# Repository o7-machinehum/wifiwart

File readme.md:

# Wifiwart
## Custom Non Form Factor Board

## Final boards

The WiFiWart is an open source WiFi penetration device masquerading as a 
wall charger. It features a 1.2Ghz Cortex A7 MPU with two WiFi
chips. The electrical, mechanical and software elemenet are all completely
open source. Check out the blog series!

- [Final Blog Post](https://interruptlabs.ca/2021/10/25/I-put-a-WiFi-router-into-a-phone-charger-Final-Post/)
- [Blog Post #3](https://interruptlabs.ca/2021/09/22/I'm-not-putting-a-WiFi-router-into-a-phone-charger-Part-3/)
- [Blog Post #2](https://interruptlabs.ca/2021/07/19/I'm-putting-a-WiFi-router-into-a-wall-charger-Part-2/)
- [Blog Post #1](https://interruptlabs.ca/2021/06/15/I'm-putting-a-WiFi-router-into-a-wall-charger-Part-1/)
- [Blog Post #0](https://interruptlabs.ca/2021/04/28/I'm-putting-a-WiFi-router-into-a-wall-charger-Part-0/)
- [Join us on Discord!](https://discord.gg/EtZT7mjNuM)

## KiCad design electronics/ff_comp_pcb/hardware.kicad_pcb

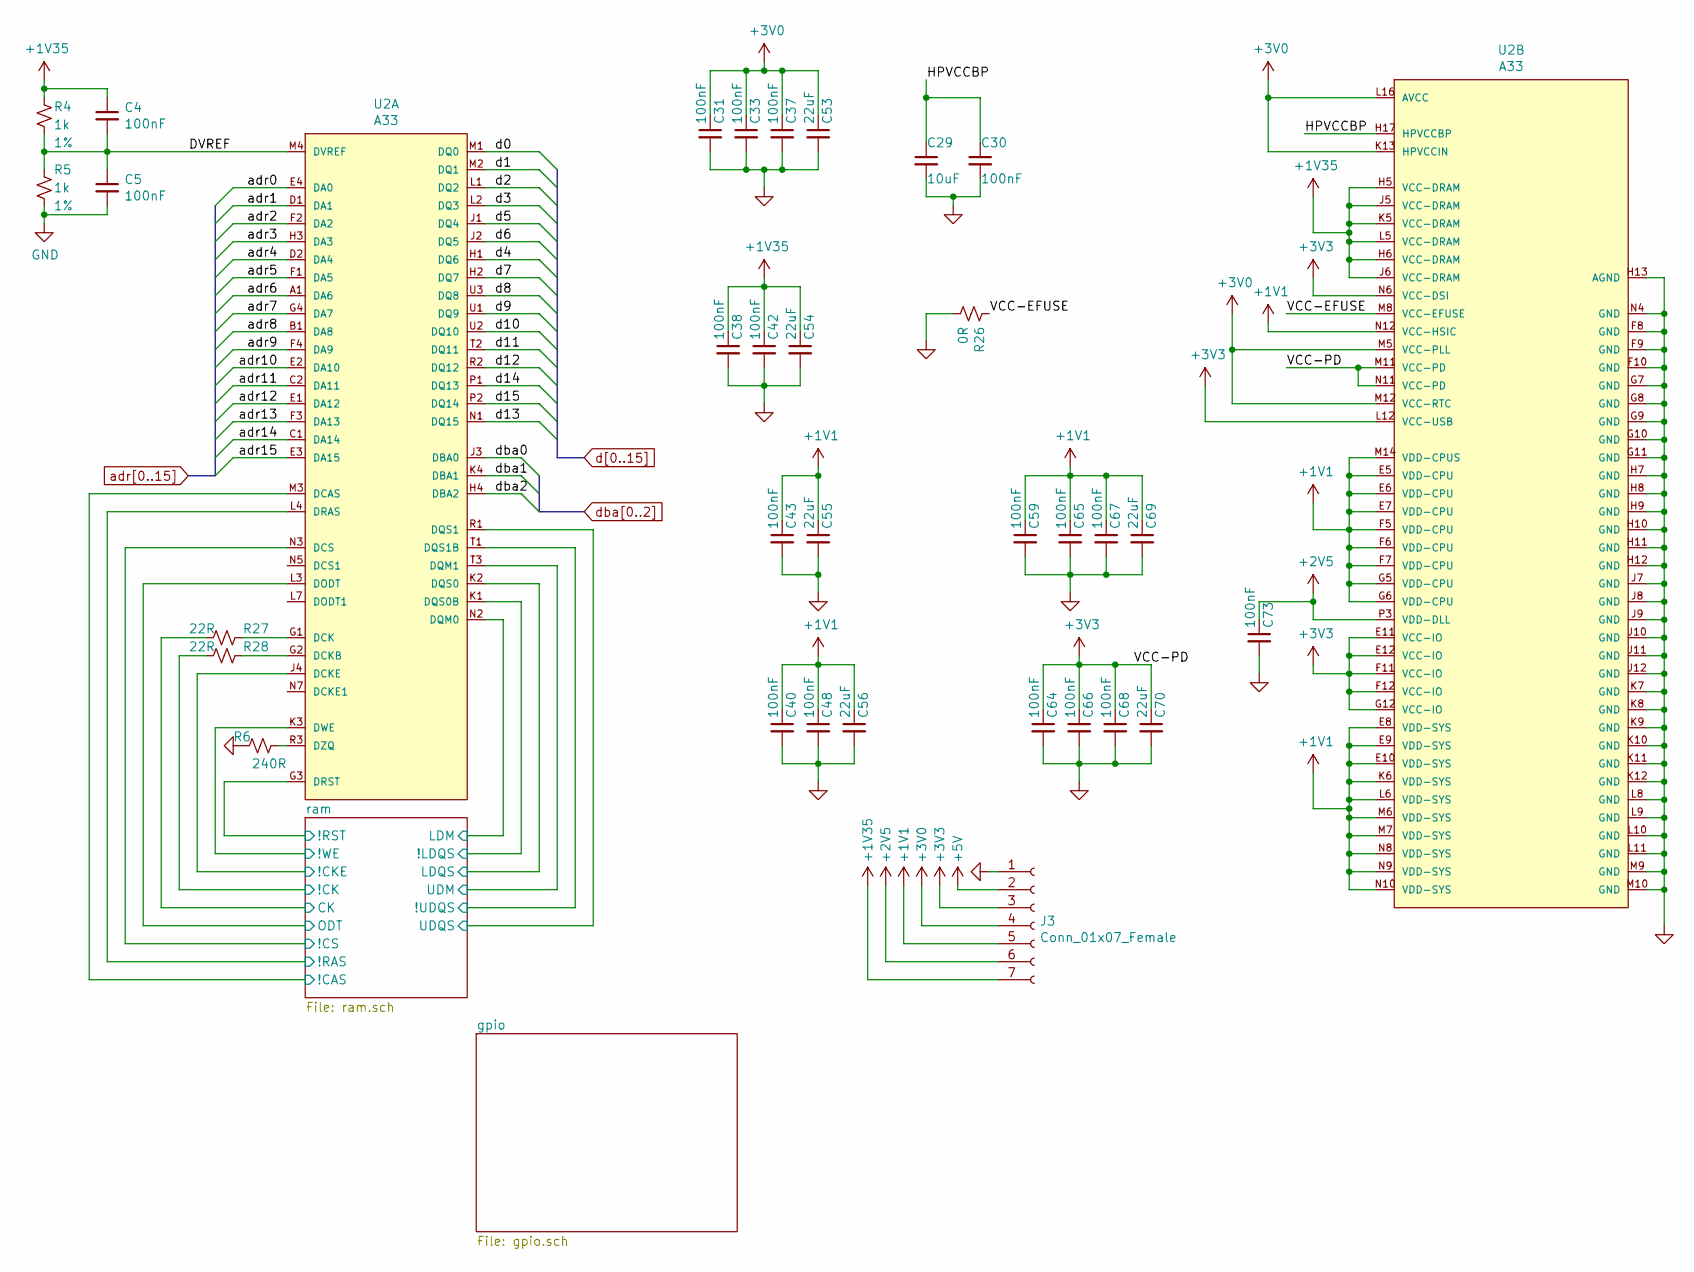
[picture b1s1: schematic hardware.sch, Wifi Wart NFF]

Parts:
C4, C5, C30, C31, C33, C37, C38, C40, C42, C43, C48, C59, C64, C65, C66, C67, C68, C73: 100nF; C_0402_1005Metric; MPN CC0402KRX7R7BB104
C29: 10uF; C_0402_1005Metric; MPN CL05A106MQ5NUNC
C53, C54, C55, C56, C69, C70: 22uF; C_0402_1005Metric; MPN GRM155R60J226ME11D
J3: Conn_01x07_Female; PinHeader_1x07_P2.54mm_Vertical
R4, R5: 1k; R_0402_1005Metric; Tolerance 1%; MPN 4-1879208-9
R6: 240R; R_0402_1005Metric; MPN 0402WGF2400TCE
R26: 0R; R_0402_1005Metric; MPN RC0402JR-070RL
R27, R28: 22R; R_0402_1005Metric; MPN RC0402JR-0722RL
U2: A33; Allwinner_Technology_Co.,_Ltd.-A33-0; MPN A33

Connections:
+1V1: C40.1, C43.1, C48.1, C55.1, C56.1, C59.1, C65.1, C67.1, C69.1, J3.5, U2.E5 (VDD-CPU), U2.E6 (VDD-CPU), U2.E7 (VDD-CPU), U2.E8 (VDD-SYS), U2.E9 (VDD-SYS), U2.E10 (VDD-SYS), U2.F5 (VDD-CPU), U2.F6 (VDD-CPU), U2.F7 (VDD-CPU), U2.G5 (VDD-CPU), U2.G6 (VDD-CPU), U2.K6 (VDD-SYS), U2.L6 (VDD-SYS), U2.M6 (VDD-SYS), U2.M7 (VDD-SYS), U2.M14 (VDD-CPUS), U2.N8 (VDD-SYS), U2.N9 (VDD-SYS), U2.N10 (VDD-SYS), U2.N12 (VCC-HSIC)
+1V35: C4.1, C38.1, C42.1, C54.1, J3.7, R4.1, U2.H5 (VCC-DRAM), U2.H6 (VCC-DRAM), U2.J5 (VCC-DRAM), U2.J6 (VCC-DRAM), U2.K5 (VCC-DRAM), U2.L5 (VCC-DRAM); also elsewhere on the board
+2V5: C73.1, J3.6, U2.P3 (VDD-DLL)
+3V0: C31.1, C33.1, C37.1, C53.1, J3.4, U2.K13 (HPVCCIN), U2.L16 (AVCC), U2.M5 (VCC-PLL), U2.M12 (VCC-RTC)
+3V3: C64.1, C66.1, C68.1, C70.1, J3.3, U2.E11 (VCC-IO), U2.E12 (VCC-IO), U2.F11 (VCC-IO), U2.F12 (VCC-IO), U2.G12 (VCC-IO), U2.L12 (VCC-USB), U2.M11 (VCC-PD), U2.N6 (VCC-DSI), U2.N11 (VCC-PD); also elsewhere on the board
+5V: J3.2; also elsewhere on the board
/DVREF: C4.2, C5.1, R4.2, R5.1, U2.M4 (DVREF)
/HPVCCBP: C29.1, C30.1, U2.H17 (HPVCCBP)
/VCC-EFUSE: R26.1, U2.M8 (VCC-EFUSE)
/ram/!CAS: U2.M3 (DCAS); also elsewhere on the board
/ram/!CK: R28.2; also elsewhere on the board
/ram/!CKE: U2.J4 (DCKE); also elsewhere on the board
/ram/!CS: U2.N3 (DCS); also elsewhere on the board
/ram/!LDQS: U2.K1 (DQS0B); also elsewhere on the board
/ram/!RAS: U2.L4 (DRAS); also elsewhere on the board
/ram/!RST: U2.G3 (DRST); also elsewhere on the board
/ram/!UDQS: U2.T1 (DQS1B); also elsewhere on the board
/ram/!WE: U2.K3 (DWE); also elsewhere on the board
/ram/CK: R27.2; also elsewhere on the board
/ram/LDM: U2.N2 (DQM0); also elsewhere on the board
/ram/LDQS: U2.K2 (DQS0); also elsewhere on the board
/ram/ODT: U2.L3 (DODT); also elsewhere on the board
/ram/UDM: U2.T3 (DQM1); also elsewhere on the board
/ram/UDQS: U2.R1 (DQS1); also elsewhere on the board
GND: C5.2, C29.2, C30.2, C31.2, C33.2, C37.2, C38.2, C40.2, C42.2, C43.2, C48.2, C53.2, C54.2, C55.2, C56.2, C59.2, C64.2, C65.2, C66.2, C67.2, C68.2, C69.2, C70.2, C73.2, J3.1, R5.2, R6.2, R26.2, U2.F8 (GND), U2.F9 (GND), U2.F10 (GND), U2.G7 (GND), U2.G8 (GND), U2.G9 (GND), U2.G10 (GND), U2.G11 (GND), U2.H7 (GND), U2.H8 (GND), U2.H9 (GND), U2.H10 (GND), U2.H11 (GND), U2.H12 (GND), U2.H13 (AGND), U2.J7 (GND), U2.J8 (GND), U2.J9 (GND), U2.J10 (GND), U2.J11 (GND), U2.J12 (GND), U2.K7 (GND), U2.K8 (GND), U2.K9 (GND), U2.K10 (GND), U2.K11 (GND), U2.K12 (GND), U2.L8 (GND), U2.L9 (GND), U2.L10 (GND), U2.L11 (GND), U2.M9 (GND), U2.M10 (GND), U2.N4 (GND); also elsewhere on the board
unnamed: R6.1, U2.R3 (DZQ)
unnamed: R27.1, U2.G1 (DCK)
unnamed: R28.1, U2.G2 (DCKB)
adr0: U2.E4 (DA0); also elsewhere on the board
adr1: U2.D1 (DA1); also elsewhere on the board
adr2: U2.F2 (DA2); also elsewhere on the board
adr3: U2.H3 (DA3); also elsewhere on the board
adr4: U2.D2 (DA4); also elsewhere on the board
adr5: U2.F1 (DA5); also elsewhere on the board
adr6: U2.A1 (DA6); also elsewhere on the board
adr7: U2.G4 (DA7); also elsewhere on the board
adr8: U2.B1 (DA8); also elsewhere on the board
adr9: U2.F4 (DA9); also elsewhere on the board
adr10: U2.E2 (DA10); also elsewhere on the board
adr11: U2.C2 (DA11); also elsewhere on the board
adr12: U2.E1 (DA12); also elsewhere on the board
adr13: U2.F3 (DA13); also elsewhere on the board
adr14: U2.C1 (DA14); also elsewhere on the board
adr15: U2.E3 (DA15); also elsewhere on the board
d0: U2.M1 (DQ0); also elsewhere on the board
d1: U2.M2 (DQ1); also elsewhere on the board
d2: U2.L1 (DQ2); also elsewhere on the board
d3: U2.L2 (DQ3); also elsewhere on the board
d4: U2.H1 (DQ6); also elsewhere on the board
d5: U2.J1 (DQ4); also elsewhere on the board
d6: U2.J2 (DQ5); also elsewhere on the board
d7: U2.H2 (DQ7); also elsewhere on the board
d8: U2.U3 (DQ8); also elsewhere on the board
d9: U2.U1 (DQ9); also elsewhere on the board
d10: U2.U2 (DQ10); also elsewhere on the board
d11: U2.T2 (DQ11); also elsewhere on the board
d12: U2.R2 (DQ12); also elsewhere on the board
d13: U2.N1 (DQ15); also elsewhere on the board
d14: U2.P1 (DQ13); also elsewhere on the board
d15: U2.P2 (DQ14); also elsewhere on the board
dba0: U2.J3 (DBA0); also elsewhere on the board
dba1: U2.K4 (DBA1); also elsewhere on the board
dba2: U2.H4 (DBA2); also elsewhere on the board

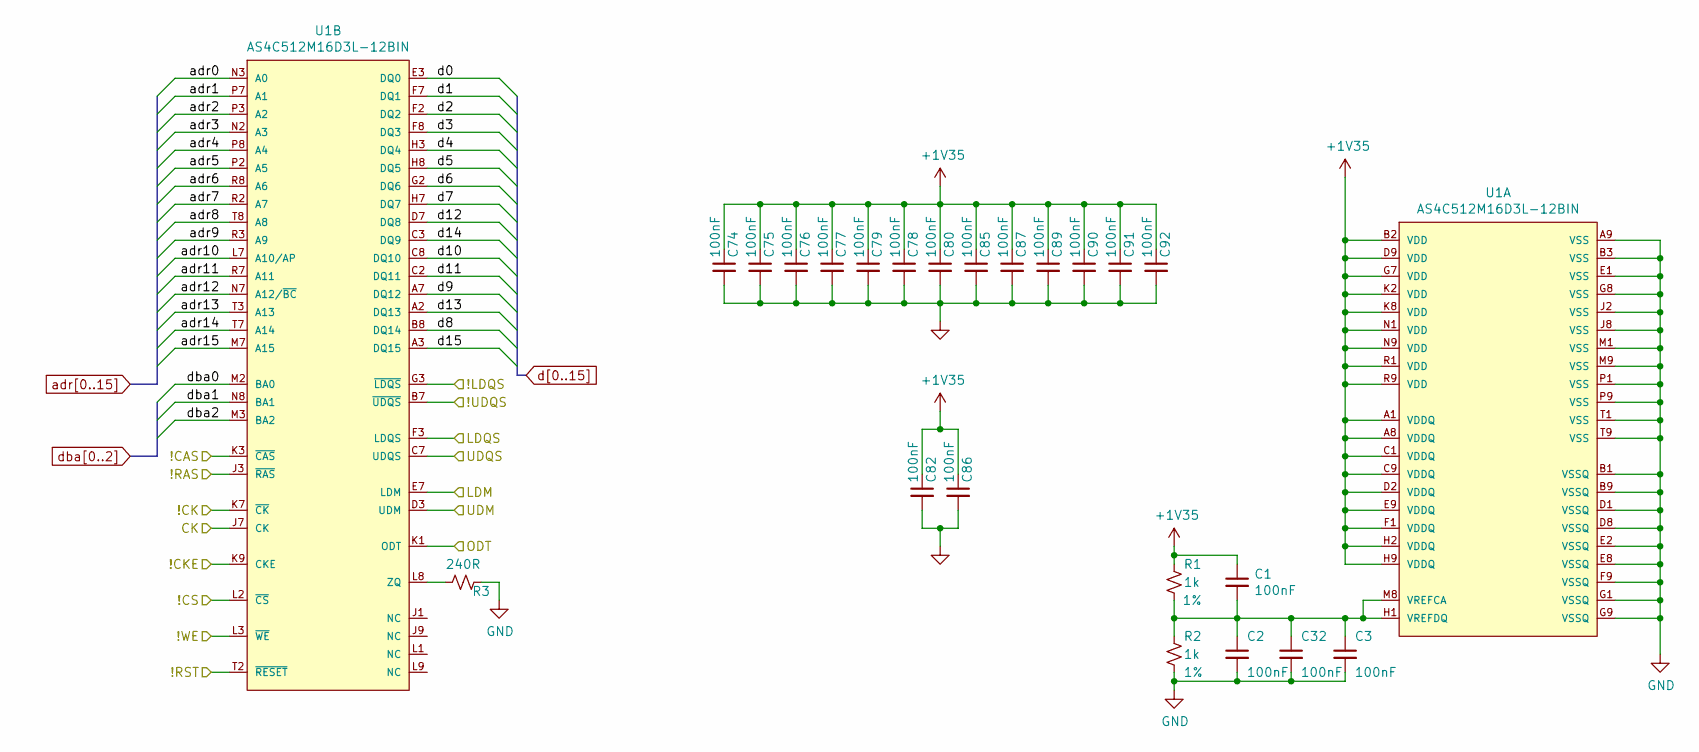
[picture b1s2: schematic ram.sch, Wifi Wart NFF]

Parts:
C1, C2, C3, C32, C74, C75, C76, C77, C78, C79, C80, C82, C85, C86, C87, C89, C90, C91, C92: 100nF; C_0402_1005Metric; MPN CC0402KRX7R7BB104
R1, R2: 1k; R_0402_1005Metric; Tolerance 1%; MPN 4-1879208-9
R3: 240R; R_0402_1005Metric; MPN 0402WGF2400TCE
U1: AS4C512M16D3L-12BIN; Alliance_Memory-AS4C512M16D3L-12BIN-0-0-IPC_A; MPN AS4C512M16D3L-12BIN

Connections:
+1V35: C1.1, C74.1, C75.1, C76.1, C77.1, C78.1, C79.1, C80.1, C82.1, C85.1, C86.1, C87.1, C89.1, C90.1, C91.1, C92.1, R1.1, U1.A1 (VDDQ), U1.A8 (VDDQ), U1.B2 (VDD), U1.C1 (VDDQ), U1.C9 (VDDQ), U1.D2 (VDDQ), U1.D9 (VDD), U1.E9 (VDDQ), U1.F1 (VDDQ), U1.G7 (VDD), U1.H2 (VDDQ), U1.H9 (VDDQ), U1.K2 (VDD), U1.K8 (VDD), U1.N1 (VDD), U1.N9 (VDD), U1.R1 (VDD), U1.R9 (VDD); also elsewhere on the board
/ram/!CAS: U1.K3 (~CAS~); also elsewhere on the board
/ram/!CK: U1.K7 (~CK~); also elsewhere on the board
/ram/!CKE: U1.K9 (CKE); also elsewhere on the board
/ram/!CS: U1.L2 (~CS~); also elsewhere on the board
/ram/!LDQS: U1.G3 (~LDQS~); also elsewhere on the board
/ram/!RAS: U1.J3 (~RAS~); also elsewhere on the board
/ram/!RST: U1.T2 (~RESET~); also elsewhere on the board
/ram/!UDQS: U1.B7 (~UDQS~); also elsewhere on the board
/ram/!WE: U1.L3 (~WE~); also elsewhere on the board
/ram/CK: U1.J7 (CK); also elsewhere on the board
/ram/LDM: U1.E7 (LDM); also elsewhere on the board
/ram/LDQS: U1.F3 (LDQS); also elsewhere on the board
/ram/ODT: U1.K1 (ODT); also elsewhere on the board
/ram/UDM: U1.D3 (UDM); also elsewhere on the board
/ram/UDQS: U1.C7 (UDQS); also elsewhere on the board
GND: C2.2, C3.2, C32.2, C74.2, C75.2, C76.2, C77.2, C78.2, C79.2, C80.2, C82.2, C85.2, C86.2, C87.2, C89.2, C90.2, C91.2, C92.2, R2.2, R3.1, U1.A9 (VSS), U1.B1 (VSSQ), U1.B3 (VSS), U1.B9 (VSSQ), U1.D1 (VSSQ), U1.D8 (VSSQ), U1.E1 (VSS), U1.E2 (VSSQ), U1.E8 (VSSQ), U1.F9 (VSSQ), U1.G1 (VSSQ), U1.G8 (VSS), U1.G9 (VSSQ), U1.J2 (VSS), U1.J8 (VSS), U1.M1 (VSS), U1.M9 (VSS), U1.P1 (VSS), U1.P9 (VSS), U1.T1 (VSS), U1.T9 (VSS); also elsewhere on the board
unnamed: C1.2, C2.1, C3.1, C32.1, R1.2, R2.1, U1.H1 (VREFDQ), U1.M8 (VREFCA)
unnamed: R3.2, U1.L8 (ZQ)
adr0: U1.N3 (A0); also elsewhere on the board
adr1: U1.P7 (A1); also elsewhere on the board
adr2: U1.P3 (A2); also elsewhere on the board
adr3: U1.N2 (A3); also elsewhere on the board
adr4: U1.P8 (A4); also elsewhere on the board
adr5: U1.P2 (A5); also elsewhere on the board
adr6: U1.R8 (A6); also elsewhere on the board
adr7: U1.R2 (A7); also elsewhere on the board
adr8: U1.T8 (A8); also elsewhere on the board
adr9: U1.R3 (A9); also elsewhere on the board
adr10: U1.L7 (A10/AP); also elsewhere on the board
adr11: U1.R7 (A11); also elsewhere on the board
adr12: U1.N7 (A12/~BC~); also elsewhere on the board
adr13: U1.T3 (A13); also elsewhere on the board
adr14: U1.T7 (A14); also elsewhere on the board
adr15: U1.M7 (A15); also elsewhere on the board
d0: U1.E3 (DQ0); also elsewhere on the board
d1: U1.F7 (DQ1); also elsewhere on the board
d2: U1.F2 (DQ2); also elsewhere on the board
d3: U1.F8 (DQ3); also elsewhere on the board
d4: U1.H3 (DQ4); also elsewhere on the board
d5: U1.H8 (DQ5); also elsewhere on the board
d6: U1.G2 (DQ6); also elsewhere on the board
d7: U1.H7 (DQ7); also elsewhere on the board
d8: U1.B8 (DQ14); also elsewhere on the board
d9: U1.A7 (DQ12); also elsewhere on the board
d10: U1.C8 (DQ10); also elsewhere on the board
d11: U1.C2 (DQ11); also elsewhere on the board
d12: U1.D7 (DQ8); also elsewhere on the board
d13: U1.A2 (DQ13); also elsewhere on the board
d14: U1.C3 (DQ9); also elsewhere on the board
d15: U1.A3 (DQ15); also elsewhere on the board
dba0: U1.M2 (BA0); also elsewhere on the board
dba1: U1.N8 (BA1); also elsewhere on the board
dba2: U1.M3 (BA2); also elsewhere on the board

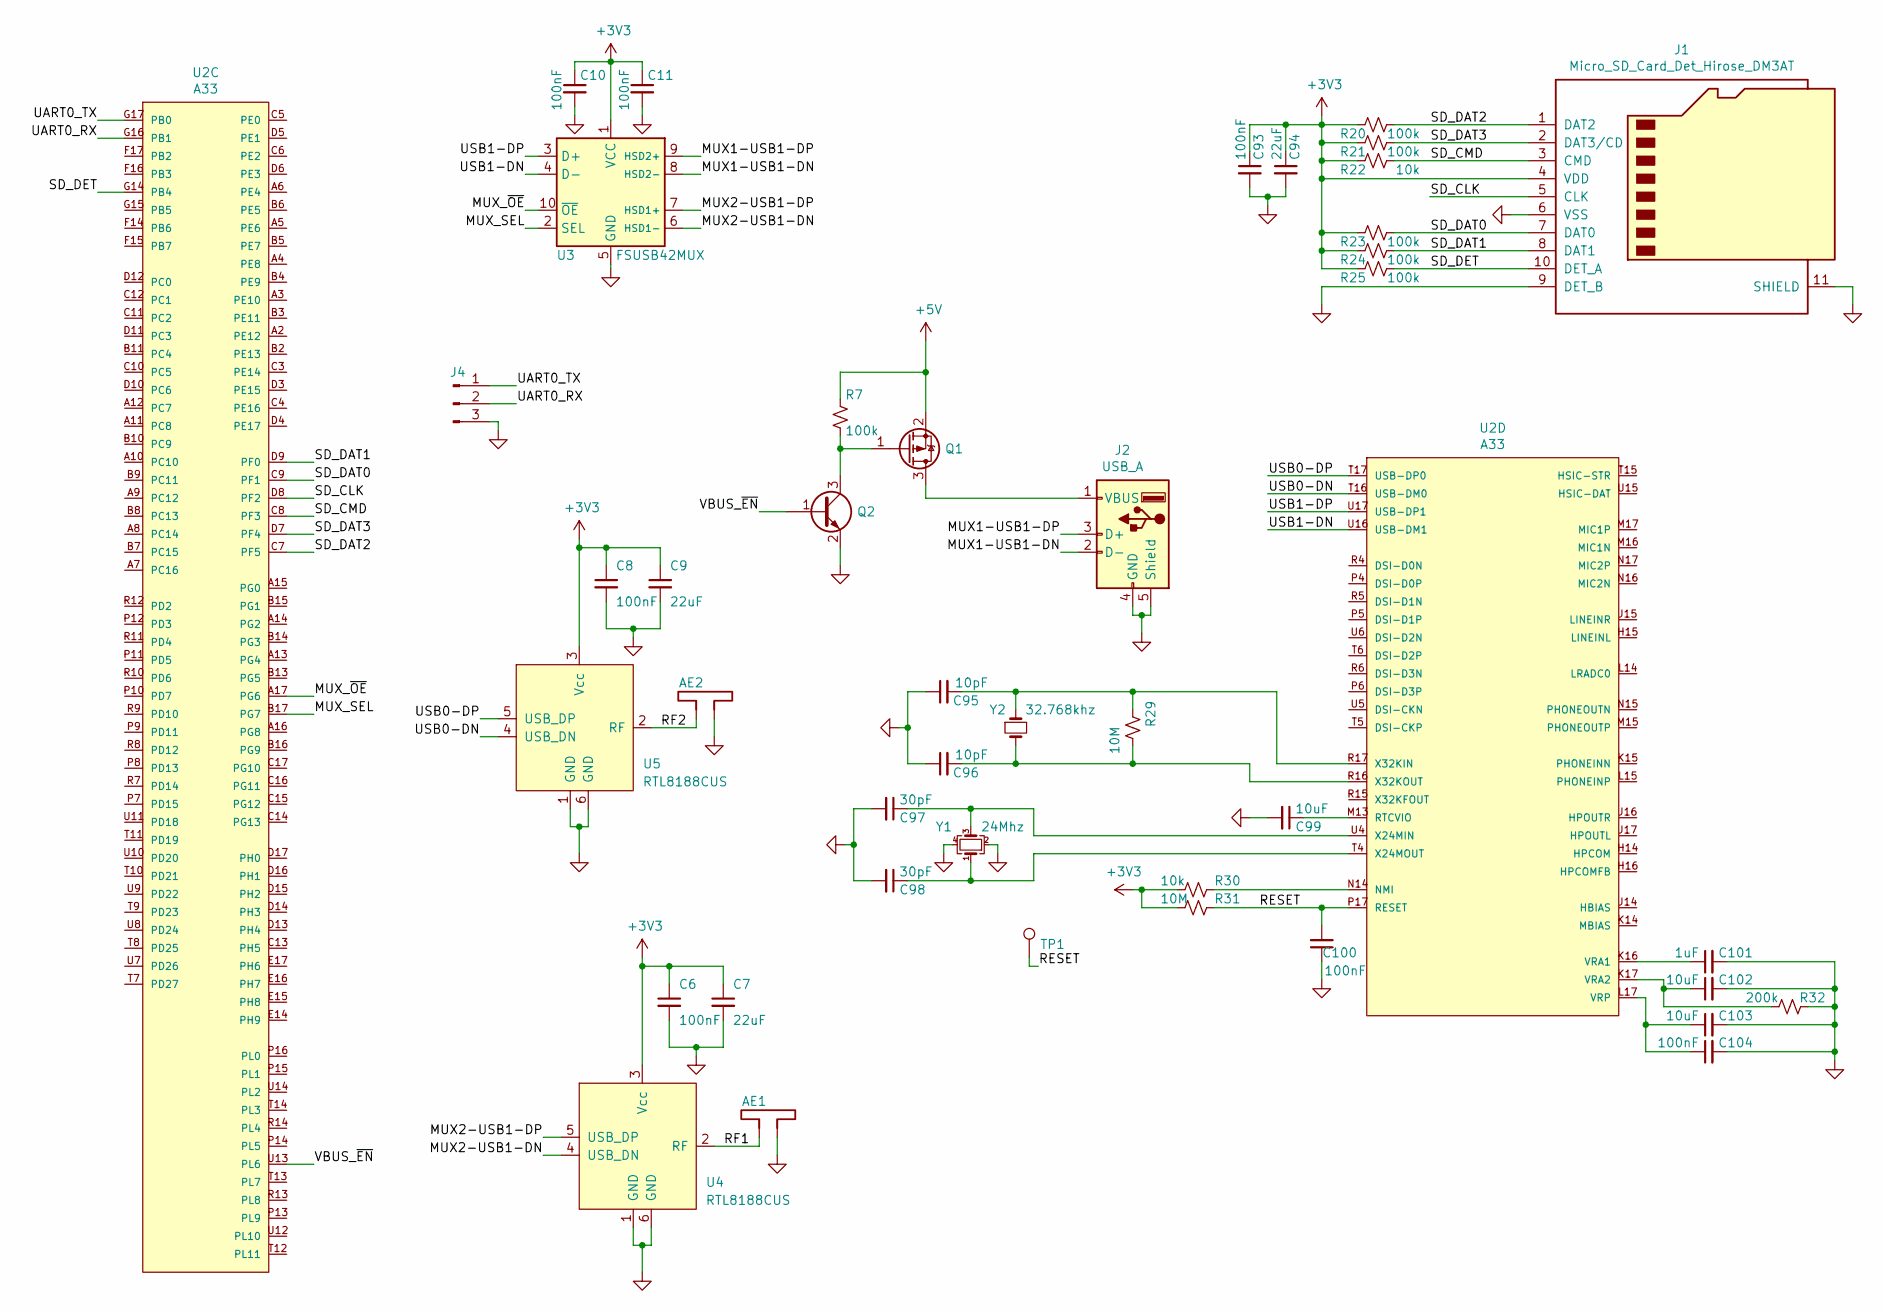
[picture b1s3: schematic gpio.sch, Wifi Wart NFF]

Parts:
AE1, AE2: Antenna_Dipole; U.FL_Hirose_U.FL-R-SMT-1_Vertical; MPN U.FL-R-SMT-1(10)
C6, C8, C10, C11, C93, C100, C104: 100nF; C_0402_1005Metric; MPN CC0402KRX7R7BB104
C7, C9, C94: 22uF; C_0402_1005Metric; MPN GRM155R60J226ME11D
C95, C96: 10pF; C_0402_1005Metric; MPN CC0402JRNPO9BN100
C97, C98: 30pF; C_0402_1005Metric; MPN CC0402JRNPO9BN300
C99, C102, C103: 10uF; C_0402_1005Metric; MPN CL05A106MQ5NUNC
C101: 1uF; C_0402_1005Metric; MPN CL05A105KO5NNNC
J1: Micro_SD_Card_Det_Hirose_DM3AT; microSD_HC_Hirose_DM3AT-SF-PEJM5; MPN DM3AT-SF-PEJM5
J2: USB_A; USB_A_Molex_67643_Horizontal; MPN 676430910
J4: Conn_01x03_Male; PinHeader_1x03_P2.54mm_Vertical
Q1: Q_PMOS_GSD; SOT-23; MPN SSM3J328R,LF
Q2: Q_NPN_BEC; SOT-23; MPN MMBT2369ALT1G
R7, R20, R21, R23, R24, R25: 100k; R_0402_1005Metric; MPN CR0402-JW-104GLF
R22, R30: 10k; R_0402_1005Metric; MPN RC0402JR-0710KL
R29, R31: 10M; R_0402_1005Metric; MPN 0402WGJ0106TCE
R32: 200k; R_0402_1005Metric; MPN RC0402FR-07200KL
TP1: TestPoint; TestPoint_Pad_2.0x2.0mm
U2: A33; Allwinner_Technology_Co.,_Ltd.-A33-0; MPN A33
U3: FSUSB42MUX; MSOP-10_3x3mm_P0.5mm; MPN FSUSB42MUX
U4, U5: RTL8188CUS; MPN RTL8188CUS
Y1: 24Mhz; Crystal_SMD_Abracon_ABM8G-4Pin_3.2x2.5mm; MPN ABM8G-24.000MHZ-18-D2Y-T
Y2: 32.768khz; Abracon-ABS05-0-0-MFG; MPN ABS05-32.768KHZ-9-T

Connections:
+3V3: C6.1, C7.1, C8.1, C9.1, C10.1, C11.1, C93.1, C94.1, J1.4 (VDD), R20.1, R21.1, R22.1, R23.1, R24.1, R25.1, R30.2, R31.2, U3.1 (VCC), U4.3 (Vcc), U5.3 (Vcc); also elsewhere on the board
+5V: Q1.2 (S), R7.1; also elsewhere on the board
/gpio/MUX1-USB1-DN: J2.2 (D-), U3.8 (HSD2-)
/gpio/MUX1-USB1-DP: J2.3 (D+), U3.9 (HSD2+)
/gpio/MUX2-USB1-DN: U3.6 (HSD1-), U4.4 (USB_DN)
/gpio/MUX2-USB1-DP: U3.7 (HSD1+), U4.5 (USB_DP)
/gpio/MUX_SEL: U2.B17 (PG7), U3.2 (SEL)
/gpio/MUX_~OE: U2.A17 (PG6), U3.10 (~OE)
/gpio/RESET: C100.2, R31.1, TP1.1, U2.P17 (RESET)
/gpio/RF1: AE1.1, U4.2 (RF)
/gpio/RF2: AE2.1, U5.2 (RF)
/gpio/SD_CLK: J1.5 (CLK), U2.D8 (PF2)
/gpio/SD_CMD: J1.3 (CMD), R22.2, U2.C8 (PF3)
/gpio/SD_DAT0: J1.7 (DAT0), R23.2, U2.C9 (PF1)
/gpio/SD_DAT1: J1.8 (DAT1), R24.2, U2.D9 (PF0)
/gpio/SD_DAT2: J1.1 (DAT2), R20.2, U2.C7 (PF5)
/gpio/SD_DAT3: J1.2 (DAT3/CD), R21.2, U2.D7 (PF4)
/gpio/SD_DET: J1.10 (DET_A), R25.2, U2.G14 (PB4)
/gpio/UART0_RX: J4.2, U2.G16 (PB1)
/gpio/UART0_TX: J4.1, U2.G17 (PB0)
/gpio/USB0-DN: U2.T16 (USB-DM0), U5.4 (USB_DN)
/gpio/USB0-DP: U2.T17 (USB-DP0), U5.5 (USB_DP)
/gpio/USB1-DN: U2.U16 (USB-DM1), U3.4 (D-)
/gpio/USB1-DP: U2.U17 (USB-DP1), U3.3 (D+)
/gpio/VBUS_~EN: Q2.1 (B), U2.U13 (PL6)
GND: AE1.2, AE2.2, C6.2, C7.2, C8.2, C9.2, C10.2, C11.2, C93.2, C94.2, C95.1, C96.1, C97.2, C98.2, C99.2, C100.1, C101.2, C102.2, C103.2, C104.2, J1.6 (VSS), J1.9 (DET_B), J1.11 (SHIELD), J2.4 (GND), J2.5 (Shield), J4.3, Q2.2 (E), R32.1, U3.5 (GND), U4.1 (GND), U4.6 (GND), U5.1 (GND), U5.6 (GND), Y1.2, Y1.4; also elsewhere on the board
unnamed: C95.2, R29.1, U2.R17 (X32KIN), Y2.1
unnamed: C96.2, R29.2, U2.R16 (X32KOUT), Y2.2
unnamed: C97.1, U2.U4 (X24MIN), Y1.3
unnamed: C98.1, U2.T4 (X24MOUT), Y1.1
unnamed: C99.1, U2.M13 (RTCVIO)
unnamed: C101.1, U2.K16 (VRA1)
unnamed: C102.1, R32.2, U2.K17 (VRA2)
unnamed: C103.1, C104.1, U2.L17 (VRP)
unnamed: J2.1 (VBUS), Q1.3 (D)
unnamed: Q1.1 (G), Q2.3 (C), R7.2
unnamed: R30.1, U2.N14 (NMI)

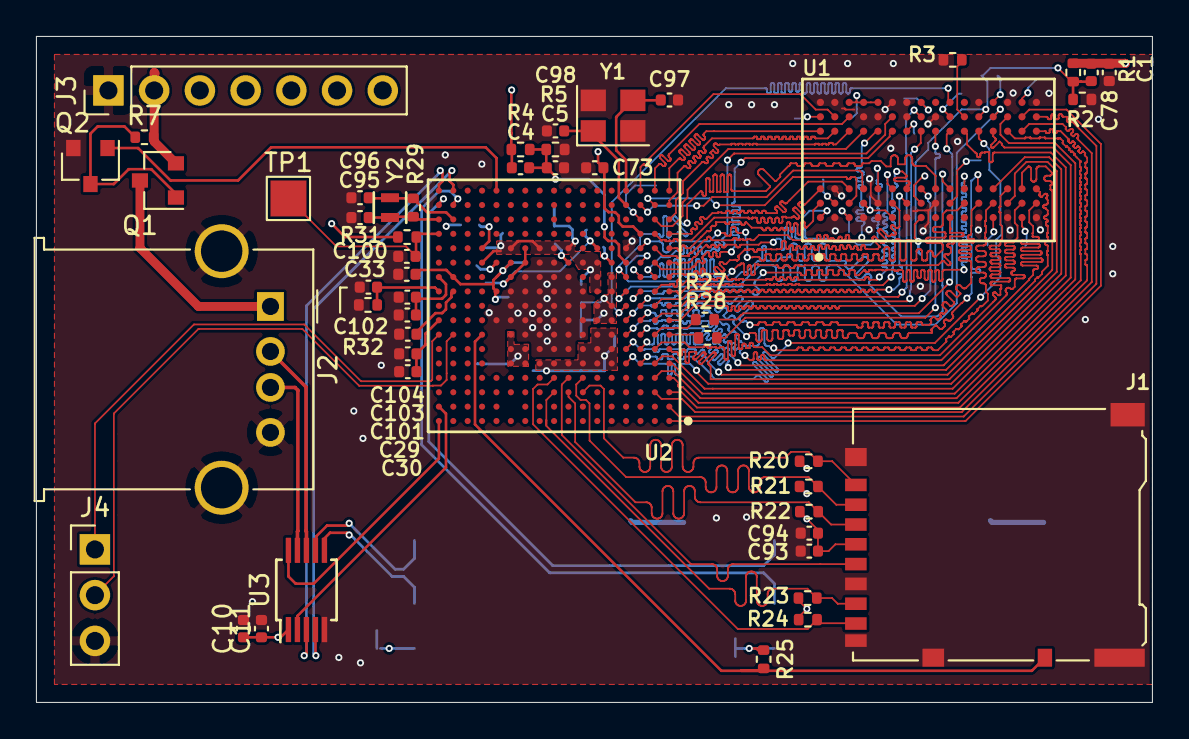
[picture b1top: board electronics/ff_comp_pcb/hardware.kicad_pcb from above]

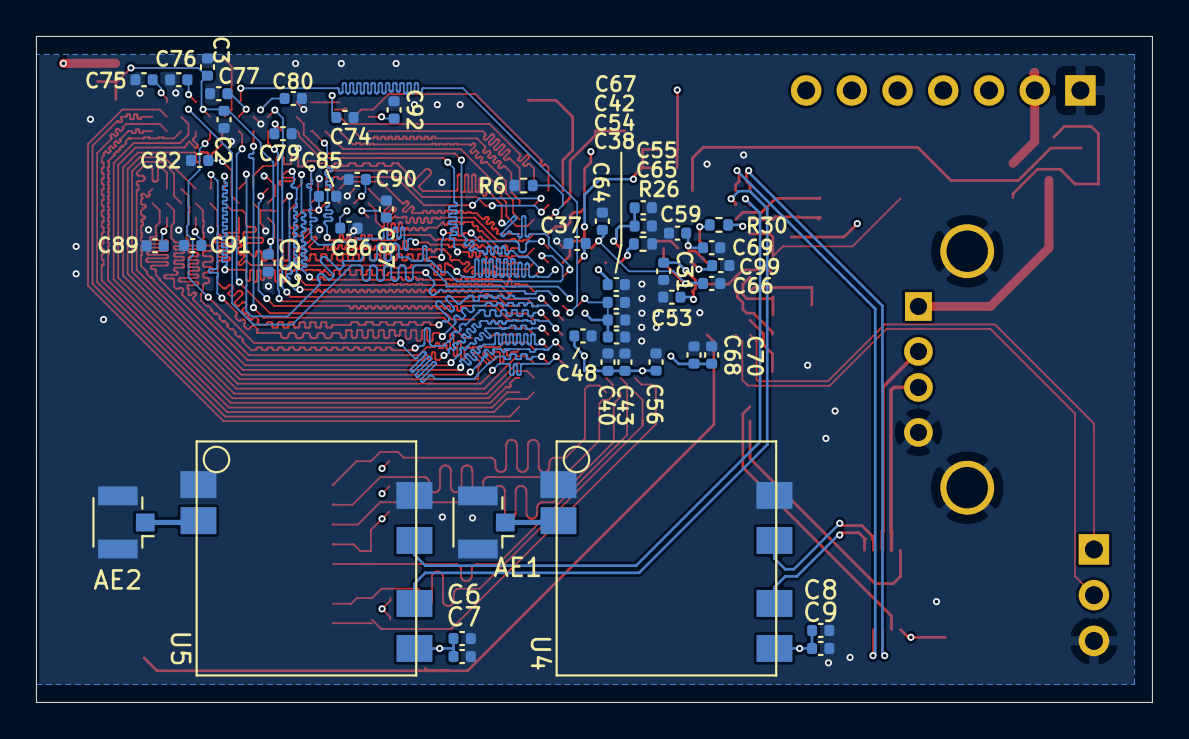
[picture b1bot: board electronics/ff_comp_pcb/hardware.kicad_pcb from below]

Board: 4 copper layers, 62.0 x 37.0 mm, 98 parts (48 on the bottom side), 99 nets.

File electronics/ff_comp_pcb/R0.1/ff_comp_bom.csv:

"Ref","Qnty","Value","Footprint","Part Number"
"AE1, AE2, ","2","Antenna_Dipole","Connector_Coaxial:U.FL_Hirose_U.FL-R-SMT-1_Vertical","U.FL-R-SMT-1(10)"
"C1, C2, C3, C4, C5, C6, C8, C10, C11, C30, C31, C32, C33, C37, C38, C40, C42, C43, C48, C59, C64, C65, C66, C67, C68, C73, C74, C75, C76, C77, C78, C79, C80, C82, C85, C86, C87, C89, C90, C91, C92, C93, C100, C104, ","44","100nF","Capacitor_SMD:C_0402_1005Metric","CC0402KRX7R7BB104"
"C7, C9, C53, C54, C55, C56, C69, C70, C94, ","9","22uF","Capacitor_SMD:C_0402_1005Metric","GRM155R60J226ME11D"
"C29, C99, C102, C103, ","4","10uF","Capacitor_SMD:C_0402_1005Metric","CL05A106MQ5NUNC"
"C95, C96, ","2","10pF","Capacitor_SMD:C_0402_1005Metric","CC0402JRNPO9BN100"
"C97, C98, ","2","30pF","Capacitor_SMD:C_0402_1005Metric","CC0402JRNPO9BN300"
"C101, ","1","1uF","Capacitor_SMD:C_0402_1005Metric","CL05A105KO5NNNC"
"J1, ","1","Micro_SD_Card_Det_Hirose_DM3AT","Connector_Card:microSD_HC_Hirose_DM3AT-SF-PEJM5","DM3AT-SF-PEJM5"
"J2, ","1","USB_A","Connector_USB:USB_A_Molex_67643_Horizontal","676430910"
"J3, ","1","Conn_01x07_Female","Connector_PinHeader_2.54mm:PinHeader_1x07_P2.54mm_Vertical",""
"J4, ","1","Conn_01x03_Male","Connector_PinHeader_2.54mm:PinHeader_1x03_P2.54mm_Vertical",""
"Q1, ","1","Q_PMOS_GSD","Package_TO_SOT_SMD:SOT-23","SSM3J328R,LF"
"Q2, ","1","Q_NPN_BEC","Package_TO_SOT_SMD:SOT-23","MMBT2369ALT1G"
"R1, R2, R4, R5, ","4","1k","Resistor_SMD:R_0402_1005Metric","4-1879208-9"
"R3, R6, ","2","240R","Resistor_SMD:R_0402_1005Metric","0402WGF2400TCE"
"R7, R20, R21, R23, R24, R25, ","6","100k","Resistor_SMD:R_0402_1005Metric","CR0402-JW-104GLF"
"R22, R30, ","2","10k","Resistor_SMD:R_0402_1005Metric","RC0402JR-0710KL"
"R26, ","1","0R","Resistor_SMD:R_0402_1005Metric","RC0402JR-070RL"
"R27, R28, ","2","22R","Resistor_SMD:R_0402_1005Metric","RC0402JR-0722RL"
"R29, R31, ","2","10M","Resistor_SMD:R_0402_1005Metric","0402WGJ0106TCE"
"R32, ","1","200k","Resistor_SMD:R_0402_1005Metric","RC0402FR-07200KL"
"TP1, ","1","TestPoint","TestPoint:TestPoint_Pad_2.0x2.0mm",""
"U1, ","1","AS4C512M16D3L-12BIN","AS4C512M16D3L:Alliance_Memory-AS4C512M16D3L-12BIN-0-0-IPC_A","AS4C512M16D3L-12BIN"
"U2, ","1","A33","A33_FP:Allwinner_Technology_Co.,_Ltd.-A33-0","A33"
"U3, ","1","FSUSB42MUX","Package_SO:MSOP-10_3x3mm_P0.5mm","FSUSB42MUX"
"U4, U5, ","2","RTL8188CUS","realtek:RTL8188CUS","RTL8188CUS"
"Y1, ","1","24Mhz","Crystal:Crystal_SMD_Abracon_ABM8G-4Pin_3.2x2.5mm","ABM8G-24.000MHZ-18-D2Y-T"
"Y2, ","1","32.768khz","Abracon:Abracon-ABS05-0-0-MFG","ABS05-32.768KHZ-9-T"

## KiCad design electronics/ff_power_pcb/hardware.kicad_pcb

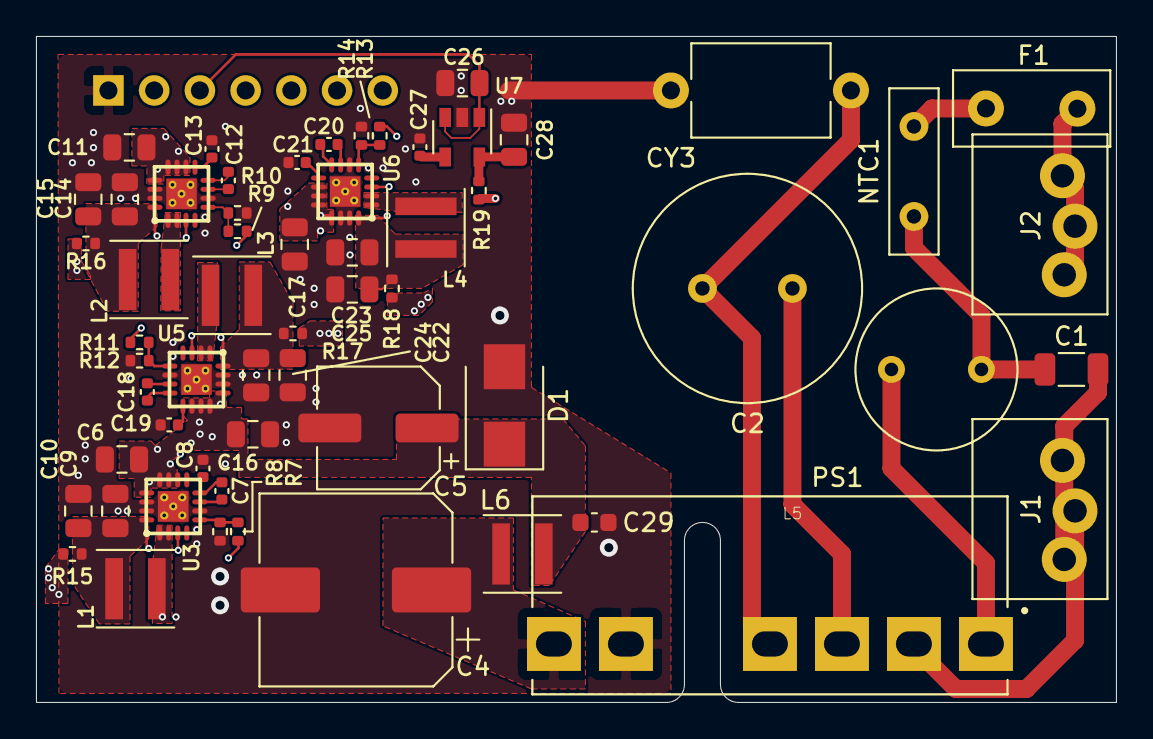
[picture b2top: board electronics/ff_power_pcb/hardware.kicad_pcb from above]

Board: 4 copper layers, 60.0 x 37.0 mm, 60 parts (1 on the bottom side), 41 nets.

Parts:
C1: 0.1uF; C_1206_3216Metric
C2: 10uF; C_Radial_D12.5mm_H20.0mm_P5.00mm
C4: 470uF; CP_Elec_10x12.5
C5: 100uF; CP_Elec_6.3x5.8
C6, C9, C10, C11, C14, C15, C16, C17, C22, C23, C24, C25: 22uF; C_0805_2012Metric
C7, C12, C18, C20: 10nF; C_0402_1005Metric
C8, C13: 450pF; C_0402_1005Metric
C19, C21: 5nF; C_0402_1005Metric
C26, C28: 10uF; C_0805_2012Metric
C27: 0.1uF; C_0402_1005Metric
C29: 0.1uF; C_0603_1608Metric
CY3: 1.0nF; C_Disc_D7.5mm_W5.0mm_P10.00mm
D1: SMBJ7.0A; D_SMB
F1: 1A/300V Slow; Fuse_Littelfuse_395Series
J1, J2: Conn_01x01_Female; IRL_00
J3: Conn_01x07_Male; PinSocket_1x07_P2.54mm_Vertical
L1, L2, L3, L4: 1uH; L_Coilcraft_XxL4020
L5: 1.2mH; RLB9012
L6: 4.7uH; L_Coilcraft_XxL4030
NTC1: 10R; C_Disc_D9.0mm_W2.5mm_P5.00mm
PS1: PBO-5C-5; CONV_PBO-5C-12
R7: 470k; R_0402_1005Metric
R8: 150k; R_0402_1005Metric
R9: 330k; R_0402_1005Metric
R10: 120k; R_0402_1005Metric
R11: 110k; R_0402_1005Metric
R12: 160k; R_0402_1005Metric
R13: 82k; R_0402_1005Metric
R14: 220k; R_0402_1005Metric
R15, R16, R17, R18, R19: 0R; R_0402_1005Metric
U3, U4, U5, U6: TPS62095RGTR; TI_RTE_S-PWQFN-N16
U7: AP131-25; SOT-23-5

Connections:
+1V1: J3.5, R18.1
+1V35: J3.7, R17.1
+2V5: J3.6, R19.1
+3V0: J3.4, R16.1
+3V3: C26.1, J3.3, R15.1, U7.1, U7.3
+5V: C5.1, C6.1, C11.1, C16.1, C17.1, C29.1, D1.1, J3.2, L6.2, U3.3, U3.10, U3.11, U3.12, U3.13, U4.3, U4.10, U4.11, U4.12, U4.13, U5.3, U5.10, U5.11, U5.12, U5.13, U6.3, U6.10, U6.11, U6.12, U6.13
/AC_L: F1.2, J2.1
/AC_N: C1.2, J1.1, PS1.2
GND: C4.2, C5.2, C6.2, C8.2, C9.2, C10.2, C11.2, C13.2, C14.2, C15.2, C16.2, C17.2, C19.2, C21.2, C22.2, C23.2, C24.2, C25.2, C26.2, C27.2, C28.2, C29.2, CY3.1, D1.2, J3.1, PS1.5, R8.2, R10.2, R12.2, R14.2, U3.6, U3.14, U3.15, U3.17, U4.6, U4.14, U4.15, U4.17, U5.6, U5.14, U5.15, U5.17, U6.6, U6.14, U6.15, U6.17, U7.2
unnamed: C1.1, L5.1, NTC1.1
unnamed: C2.1, PS1.3
unnamed: C2.2, CY3.2, PS1.4
unnamed: C4.1, L6.1, PS1.6
unnamed: C7.1, U3.7
unnamed: C7.2, U3.8
unnamed: C8.1, U3.9
unnamed: C9.1, C10.1, L1.2, R7.1, R15.2, U3.16
unnamed: C12.1, U4.7
unnamed: C12.2, U4.8
unnamed: C13.1, U4.9
unnamed: C14.1, C15.1, L2.2, R9.1, R16.2, U4.16
unnamed: C18.1, U5.7
unnamed: C18.2, U5.8
unnamed: C19.1, U5.9
unnamed: C20.1, U6.7
unnamed: C20.2, U6.8
unnamed: C21.1, U6.9
unnamed: C22.1, C24.1, L3.2, R11.1, R17.2, U5.16
unnamed: C23.1, C25.1, L4.2, R13.1, R18.2, U6.16
unnamed: C27.1, U7.4
unnamed: C28.1, R19.2, U7.5
unnamed: F1.1, NTC1.2
unnamed: L1.1, U3.1, U3.2
unnamed: L2.1, U4.1, U4.2
unnamed: L3.1, U5.1, U5.2
unnamed: L4.1, U6.1, U6.2
unnamed: L5.2, PS1.1
unnamed: R7.2, R8.1, U3.5
unnamed: R9.2, R10.1, U4.5
unnamed: R11.2, R12.1, U5.5
unnamed: R13.2, R14.1, U6.5

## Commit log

2021-03-17 init
2021-03-18 Finished up all the switching power supplies.
2021-03-18 Added the inductor PN in and dropped them on the board.
2021-03-18 Edited the readme
2021-03-18 Finished connecting up the RAM
2021-03-18 Added the 2.5V LDO
2021-03-18 Added datasheet
2021-03-19 Nothing really
2021-03-23 Wired in the SD card
2021-03-24 Random unknown commit
2021-03-25 Wired in the VCC-EFUSE stuff.
2021-03-25 Decoupled the ram and A33
2021-03-25 Decoupled the SD card.
2021-03-25 Just dropped all the parts on the board.
2021-03-25 Added in the mains to 5V module, this will most likely be removed in the future.
2021-03-25 Updating the readme.
2021-03-30 Figured out all the crystals
2021-03-30 Random commit
2021-03-30 Those pins have been dealt with.
2021-03-30 Wired in the NMI and reset pins.
2021-03-30 Wired in some bias pins, not sure if these are needed or not?
2021-03-31 Wired in the USB connectors.
2021-03-31 readme
2021-04-02 Backing up
2021-04-04 Repositioned the ram.
2021-04-06 RAM hooked up
2021-04-06 Working on the layout
2021-04-07 Ram finally hooked up
2021-04-13 Sync
2021-04-13 All address buses length matched
2021-04-13 Unsaved changes.
2021-04-16 Length matching finally "complete"
2021-04-16 Added in the model for the 2x USB's
2021-04-19 Working on the power supplies
2021-04-20 Updated cache file
2021-04-22 Working on the routing.
2021-04-22 Routing power supplies
2021-04-26 Working on silkscreen/placement
2021-04-27 Working on the board
2021-04-29 Working on the routing
2021-04-29 Still working on the routing.
2021-04-30 Leftover changes
2021-04-30 Added license
2021-04-30 updated the readme
2021-04-30 fixed image
2021-04-30 Filled out the license
2021-04-30 Routing
2021-05-04 Moving stuff around
2021-05-04 Moving stuff around again
2021-05-04 Still moving still moving
2021-05-04 Working on getting all the DRC out.
2021-05-04 Forgot to save
2021-05-05 Schematic review.
2021-05-06 Added tolerances
2021-05-06 Working through the checklist
2021-05-10 Checking off the list
2021-05-10 Reworked 3.3V
2021-05-10 Pulled out reset line
2021-05-10 Schematic review complete
2021-05-12 Working on the length matching
2021-05-12 Length matching finished, again lol
2021-05-12 Fixed DRC, moved silk around.
2021-05-13 DRC + BOM script
2021-05-13 cleaning up MPN
2021-05-13 Removed all the extra fields
2021-05-13 Added in all the part numbers
2021-05-13 Working on the script
2021-05-13 Part numbers are _properly_ in now.
2021-05-14 Added gerbers.
2021-05-17 Rendered more gerbers
2021-05-17 R0.1 Purchased.
2021-05-17 Forgot to save files.
2021-05-20 Added some initial cad.
2021-05-21 Added some prong holes
2021-05-26 Made some changes to the mech and added a Gantt and notes.
2021-05-26 Moved some files around.
2021-05-26 Added discord link
2021-05-26 Changed the copy
2021-05-26 Added a picture.
2021-05-26 Just another rename.
2021-05-26 First stab at the ff power board.
2021-05-26 Roughed in the transformer and whatnot.
2021-05-26 Plotting schematics for R0.1
2021-05-26 Changed sheet labels.
2021-05-26 Just made some notes, added apower budget.
2021-05-26 Just changed the path
2021-05-26 Just added some pictures.
2021-05-27 Added the compute board.
2021-05-27 Added the model for the usb, added a USB mux
2021-05-27 Updated discord link
2021-05-28 Added the realtek wifi modules
2021-05-31 Fit the radios on the board.
2021-05-31 Added the step file of the board to the model, added a u.fl connector in.
2021-05-31 Dropped down the board to board.
2021-06-01 Put a mounting hole in the board.
2021-06-01 Fit the board into the volume
2021-06-01 Initial power board in the CAD.
2021-06-01 Added the A33 UM
2021-06-01 Working on the CAD.
2021-06-05 Added some notes.
2021-06-05 Dopped all the parts down for the power supply.
2021-06-05 Added an app note of ntc current limiting, and added some part numbers into the schematic.
2021-06-06 Moved an app note into the app notes folder
2021-06-06 Dropping the parts into the layout.
2021-06-07 All footprints are in.
2021-06-07 Dropped in the power board with all the new components.
2021-06-07 Shortened the legs of an inductor.
2021-06-08 Fit all the regulators into the power board.
2021-06-09 Leftover commit
2021-06-10 Added the patch antenna.
2021-06-11 Added some pictures.
2021-06-16 Removed some pictures
2021-06-16 Added some pictures
2021-06-16 Notes from the build
2021-06-24 Added nff schematic.
2021-06-24 Added an IRC Log.
2021-07-13 Changed out the 15W supply for a 5W.
2021-07-23 Added a dumb linux video
2021-07-23 Made some changes to the readme
2021-07-23 Added some datasheets.
2021-07-23 Updated the gitignore
2021-07-23 Working on the electronics for the FF revision.
2021-07-26 Added some stuff for the contacts
2021-07-26 Added mains blade connector.
2021-08-04 Added step files, Working on the power board.
2021-08-04 Alligned the blade connectors
2021-08-06 Finished up the routing on the power board, still needs a double check.
2021-08-06 Added a fet to switching the 5V.
2021-08-07 Power distrobution IP on the CPU board. Transistors in for 5V control. Part numbers in.
2021-08-23 Random changes.
2021-08-24 Routing the MCU board.
2021-08-24 Finished layout.
2021-08-28 Worked on the routing.
2021-08-29 Generated gerbers for R0.1 power board.
2021-08-29 Added BOM for R0.1
2021-08-29 Rerouted the power traces for R0.1 power pcb - they didn't match the compute PCB power pins.
2021-08-29 Added gerbers for R0.1 comp pcb.
2021-08-30 Imported the new boards
2021-08-30 Added wifi chip part numbers
2021-09-01 Updated the bom generation scripts, updated the BOM's and added a step file.
2021-09-01 Just a rename.
2021-09-03 Added Screw Bosses.
2021-09-03 Headers were not aligned in comp_pcb, alligned them, created R0.2 and imported into assembly.
2021-10-17 Added hole for SD card and two holes for the prongs.
2021-10-19 Updated the regulator to the proper value.
2021-10-19 Revert
2021-10-29 Added some images and changed the readme
2021-11-03 Added Schematics
2021-11-03 added stl files
2022-03-25 Updated the image
2022-03-25 Typo
